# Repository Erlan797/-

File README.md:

Трассировка супер стабильного источника питания.

Принципиальная схема источника питания:

Печатная плата:

Печатная плата в 3D:

Вид спереди:

Вид сзади:

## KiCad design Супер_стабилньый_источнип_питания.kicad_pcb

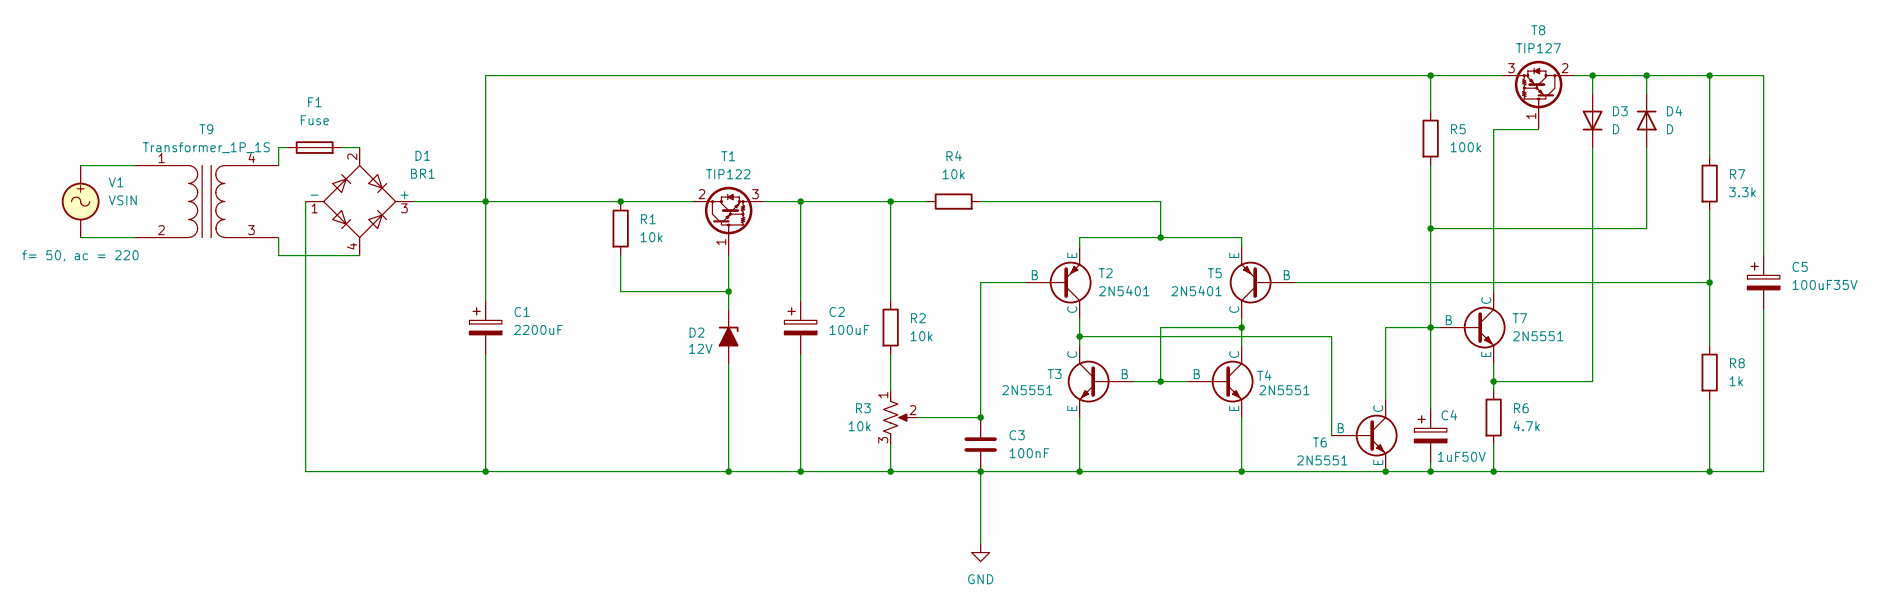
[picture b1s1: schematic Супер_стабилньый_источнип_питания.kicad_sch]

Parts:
C1: 2200uF; C_Radial_D10.0mm_H16.0mm_P5.00mm
C2: 100uF; C_Radial_D10.0mm_H16.0mm_P5.00mm
C3: 100nF; C_Disc_D5.0mm_W2.5mm_P2.50mm
C4: 1uF50V; C_Radial_D10.0mm_H16.0mm_P5.00mm
C5: 100uF35V; C_Radial_D10.0mm_H16.0mm_P5.00mm
D1: BR1; Diode_Bridge_Vishay_KBL
D2: 12V; D_DO-34_SOD68_P7.62mm_Horizontal
D3, D4: D; D_DO-34_SOD68_P7.62mm_Horizontal
F1: Fuse; Fuse_Littelfuse-LVR100
R1, R2, R4: 10k; R_Axial_DIN0204_L3.6mm_D1.6mm_P7.62mm_Horizontal
R3: 10k; Potentiometer_Alpha_RD901F-40-00D_Single_Vertical_CircularH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
R5: 100k; R_Axial_DIN0204_L3.6mm_D1.6mm_P7.62mm_Horizontal
R6: 4.7k; R_Axial_DIN0204_L3.6mm_D1.6mm_P7.62mm_Horizontal
R7: 3.3k; R_Axial_DIN0204_L3.6mm_D1.6mm_P7.62mm_Horizontal
R8: 1k; R_Axial_DIN0204_L3.6mm_D1.6mm_P7.62mm_Horizontal
T1: TIP122; TO-220-3_Vertical
T2, T5: 2N5401; TO-92_Inline
T3, T4, T6, T7: 2N5551; TO-92_Inline
T8: TIP127; TO-220-3_Vertical
T9: Transformer_1P_1S; 220V-24V
V1: VSIN

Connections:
GND: C1.2, C2.2, C3.2, C4.2, C5.2, D1.1 (-), D2.2 (A), R3.3, R6.2, R8.2, T3.3 (E), T4.3 (E), T6.3 (E)
unnamed: C1.1, D1.3 (+), R1.1, R5.1, T1.2 (C), T8.3 (E)
unnamed: D1.2, F1.2
unnamed: D2.1 (K), R1.2, T1.1 (B)
unnamed: C5.1, D3.2 (A), D4.1 (K), R7.1, T8.2 (C)
unnamed: D3.1 (K), R6.1, T7.3 (E)
unnamed: C4.1, D4.2 (A), R5.2, T6.1 (C), T7.2 (B)
unnamed: R2.2, R3.1
unnamed: C2.1, R2.1, R4.1, T1.3 (E)
unnamed: C3.1, R3.2, T2.2 (B)
unnamed: T2.1 (C), T3.1 (C), T6.2 (B)
unnamed: R4.2, T2.3 (E), T5.3 (E)
unnamed: T3.2 (B), T4.1 (C), T4.2 (B), T5.1 (C)
unnamed: R7.2, R8.1, T5.2 (B)
unnamed: T7.1 (C), T8.1 (B)
unnamed: T9.1 (AA), V1.1
unnamed: T9.2 (AB), V1.2
unnamed: D1.4, T9.3 (SA)
unnamed: F1.1, T9.4 (SB)

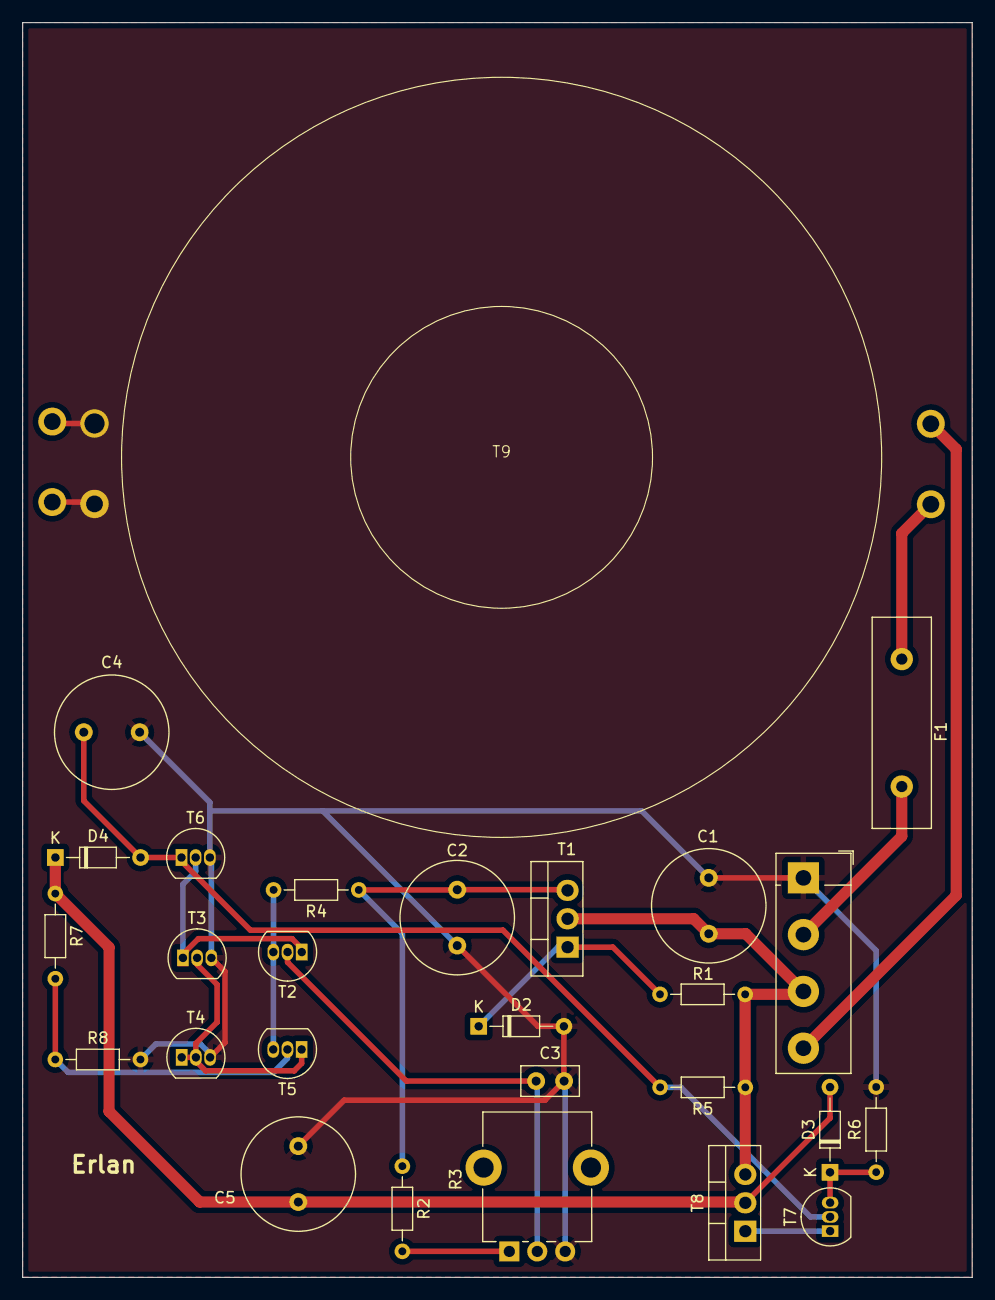
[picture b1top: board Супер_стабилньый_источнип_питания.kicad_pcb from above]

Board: 2 copper layers, 84.9 x 112.2 mm, 28 parts (0 on the bottom side), 19 nets.
